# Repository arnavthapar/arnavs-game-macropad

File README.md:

# Arnav's Game Macropad

Submission for Hackpad.

This is a macropad built for playing games. It has an OLED screen, allowing smaller games to be shown. There are 6 buttons, which can be used as the 4 directions and then 2 more for other actions.

Features:

- OLED Screen
- 6 Buttons
- SK6812 Mini LED

BOM:

- 0.91in OLED Screen
- 6x Cherry MX Switches
- 6x Blank DSA Keycaps
- SK6812 MINI LED
- XIAO RP2040
- 3d Printed Case (Top and Bottom)
- 4x Bolts

## Schematic

## PCB

The dimensions of the PCB are 65 mm by 92.5 mm.

## Case

## 3D Model

This is a estimate of what the final product should probably look like.

## Assembly

Assembling will not take very long. Once the PCB is completed (the OLED screen, XIAO, and buttons are all connected), it should be able to be put into the case. Then you can put the top of the case on, and it's done.

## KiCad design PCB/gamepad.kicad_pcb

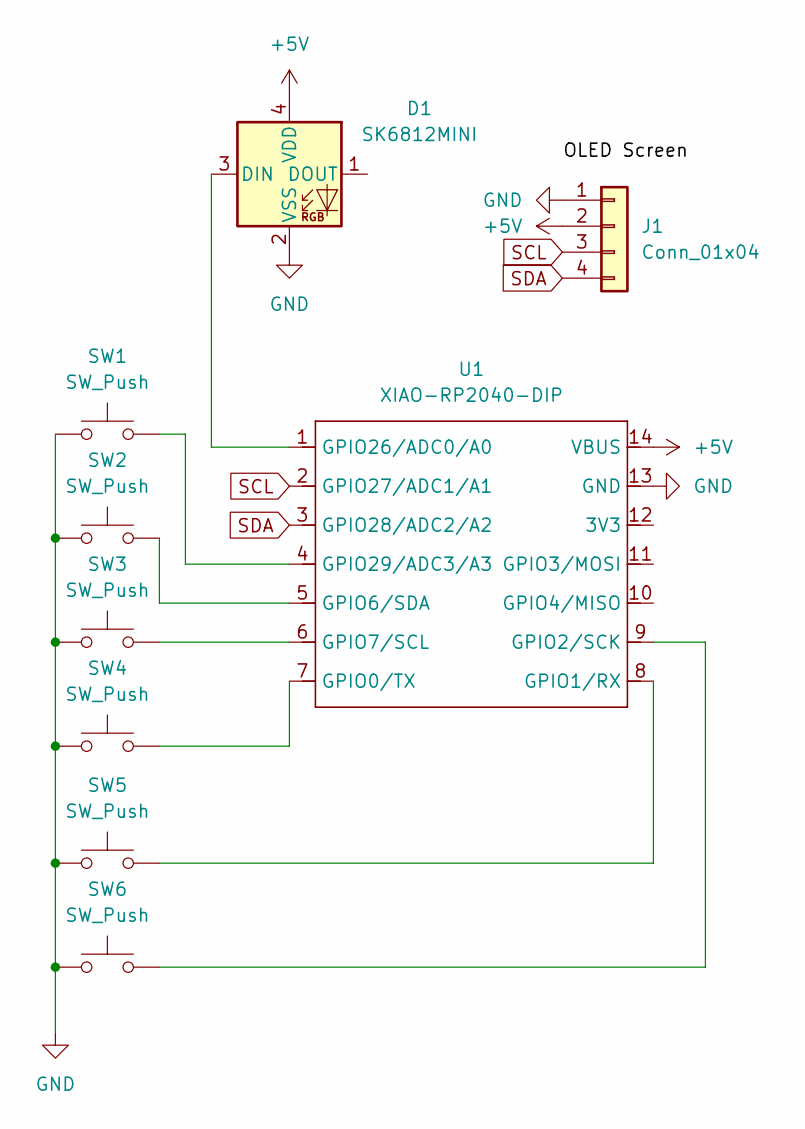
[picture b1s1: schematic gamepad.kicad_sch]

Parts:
D1: SK6812MINI; LED_SK6812MINI_PLCC4_3.5x3.5mm_P1.75mm
J1: Conn_01x04; PinHeader_1x04_P2.54mm_Vertical
SW1, SW2, SW3, SW4, SW5, SW6: SW_Push; SW_Cherry_MX_1.00u_PCB
U1: XIAO-RP2040-DIP

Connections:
+5V: D1.4 (VDD), J1.2, U1.14 (VBUS)
GND: D1.2 (VSS), J1.1, SW1.1, SW2.1, SW3.1, SW4.1, SW5.1, SW6.1, U1.13 (GND)
unnamed: D1.3 (DIN), U1.1 (GPIO26/ADC0/A0)
unnamed: SW4.2, U1.7 (GPIO0/TX)
unnamed: SW5.2, U1.8 (GPIO1/RX)
unnamed: SW6.2, U1.9 (GPIO2/SCK)
unnamed: SW2.2, U1.5 (GPIO6/SDA)
unnamed: SW3.2, U1.6 (GPIO7/SCL)
unnamed: SW1.2, U1.4 (GPIO29/ADC3/A3)
SCL: J1.3, U1.2 (GPIO27/ADC1/A1)
SDA: J1.4, U1.3 (GPIO28/ADC2/A2)

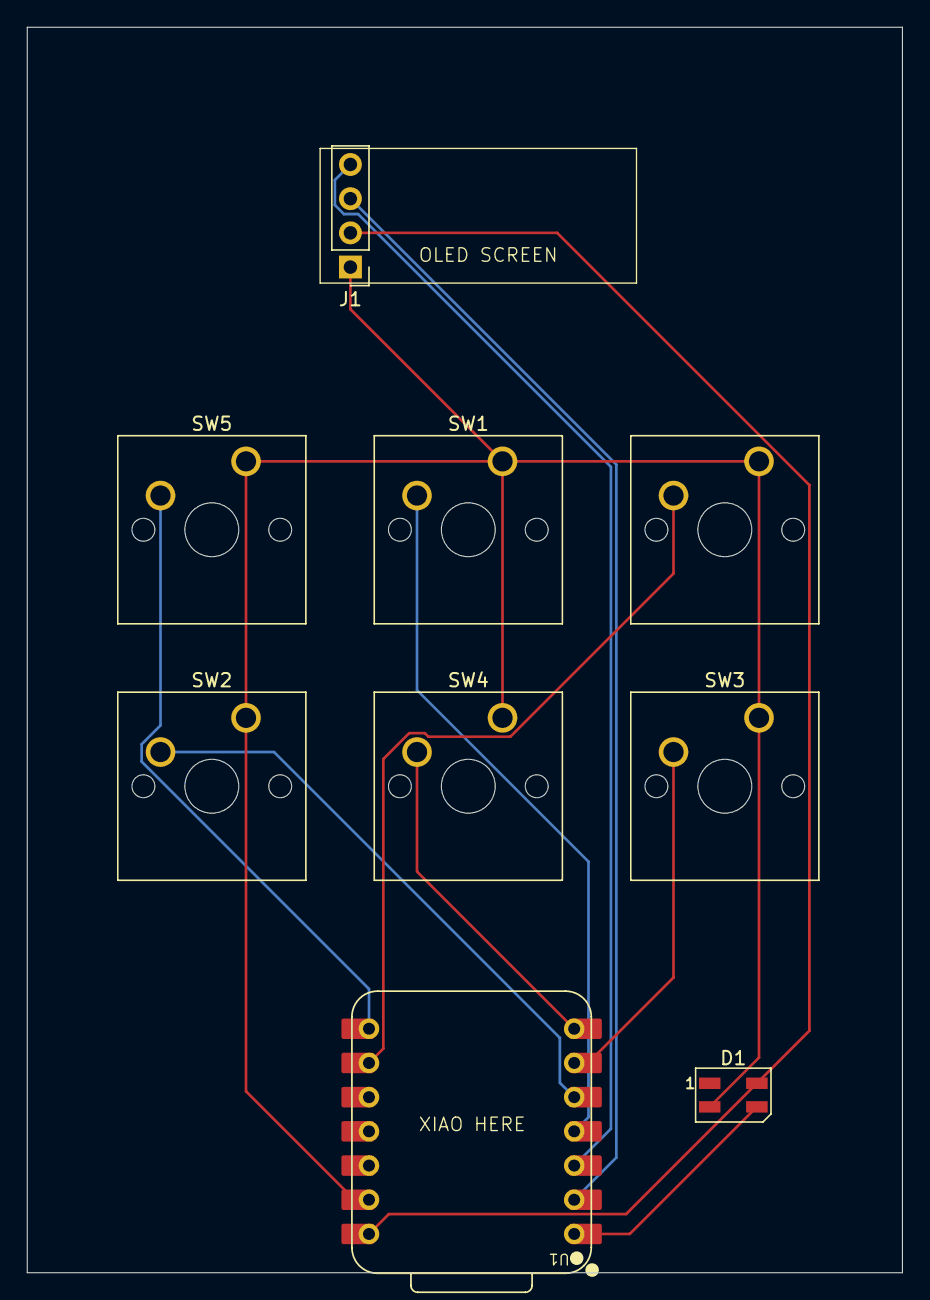
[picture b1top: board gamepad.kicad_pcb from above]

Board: 2 copper layers, 65.0 x 92.5 mm, 9 parts (0 on the bottom side), 11 nets.

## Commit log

2025-12-02 add pcb
2025-12-02 fix images
2025-12-02 add BOM
2025-12-02 start firmware
2025-12-03 pcb edit
2025-12-03 case
2025-12-03 case edit
2025-12-03 firmware add
2025-12-03 firmware fix
2025-12-03 case fix
2025-12-04 model
2025-12-04 fix image
2025-12-04 turn oled
2025-12-04 images

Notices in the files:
README.md:
License: MIT
